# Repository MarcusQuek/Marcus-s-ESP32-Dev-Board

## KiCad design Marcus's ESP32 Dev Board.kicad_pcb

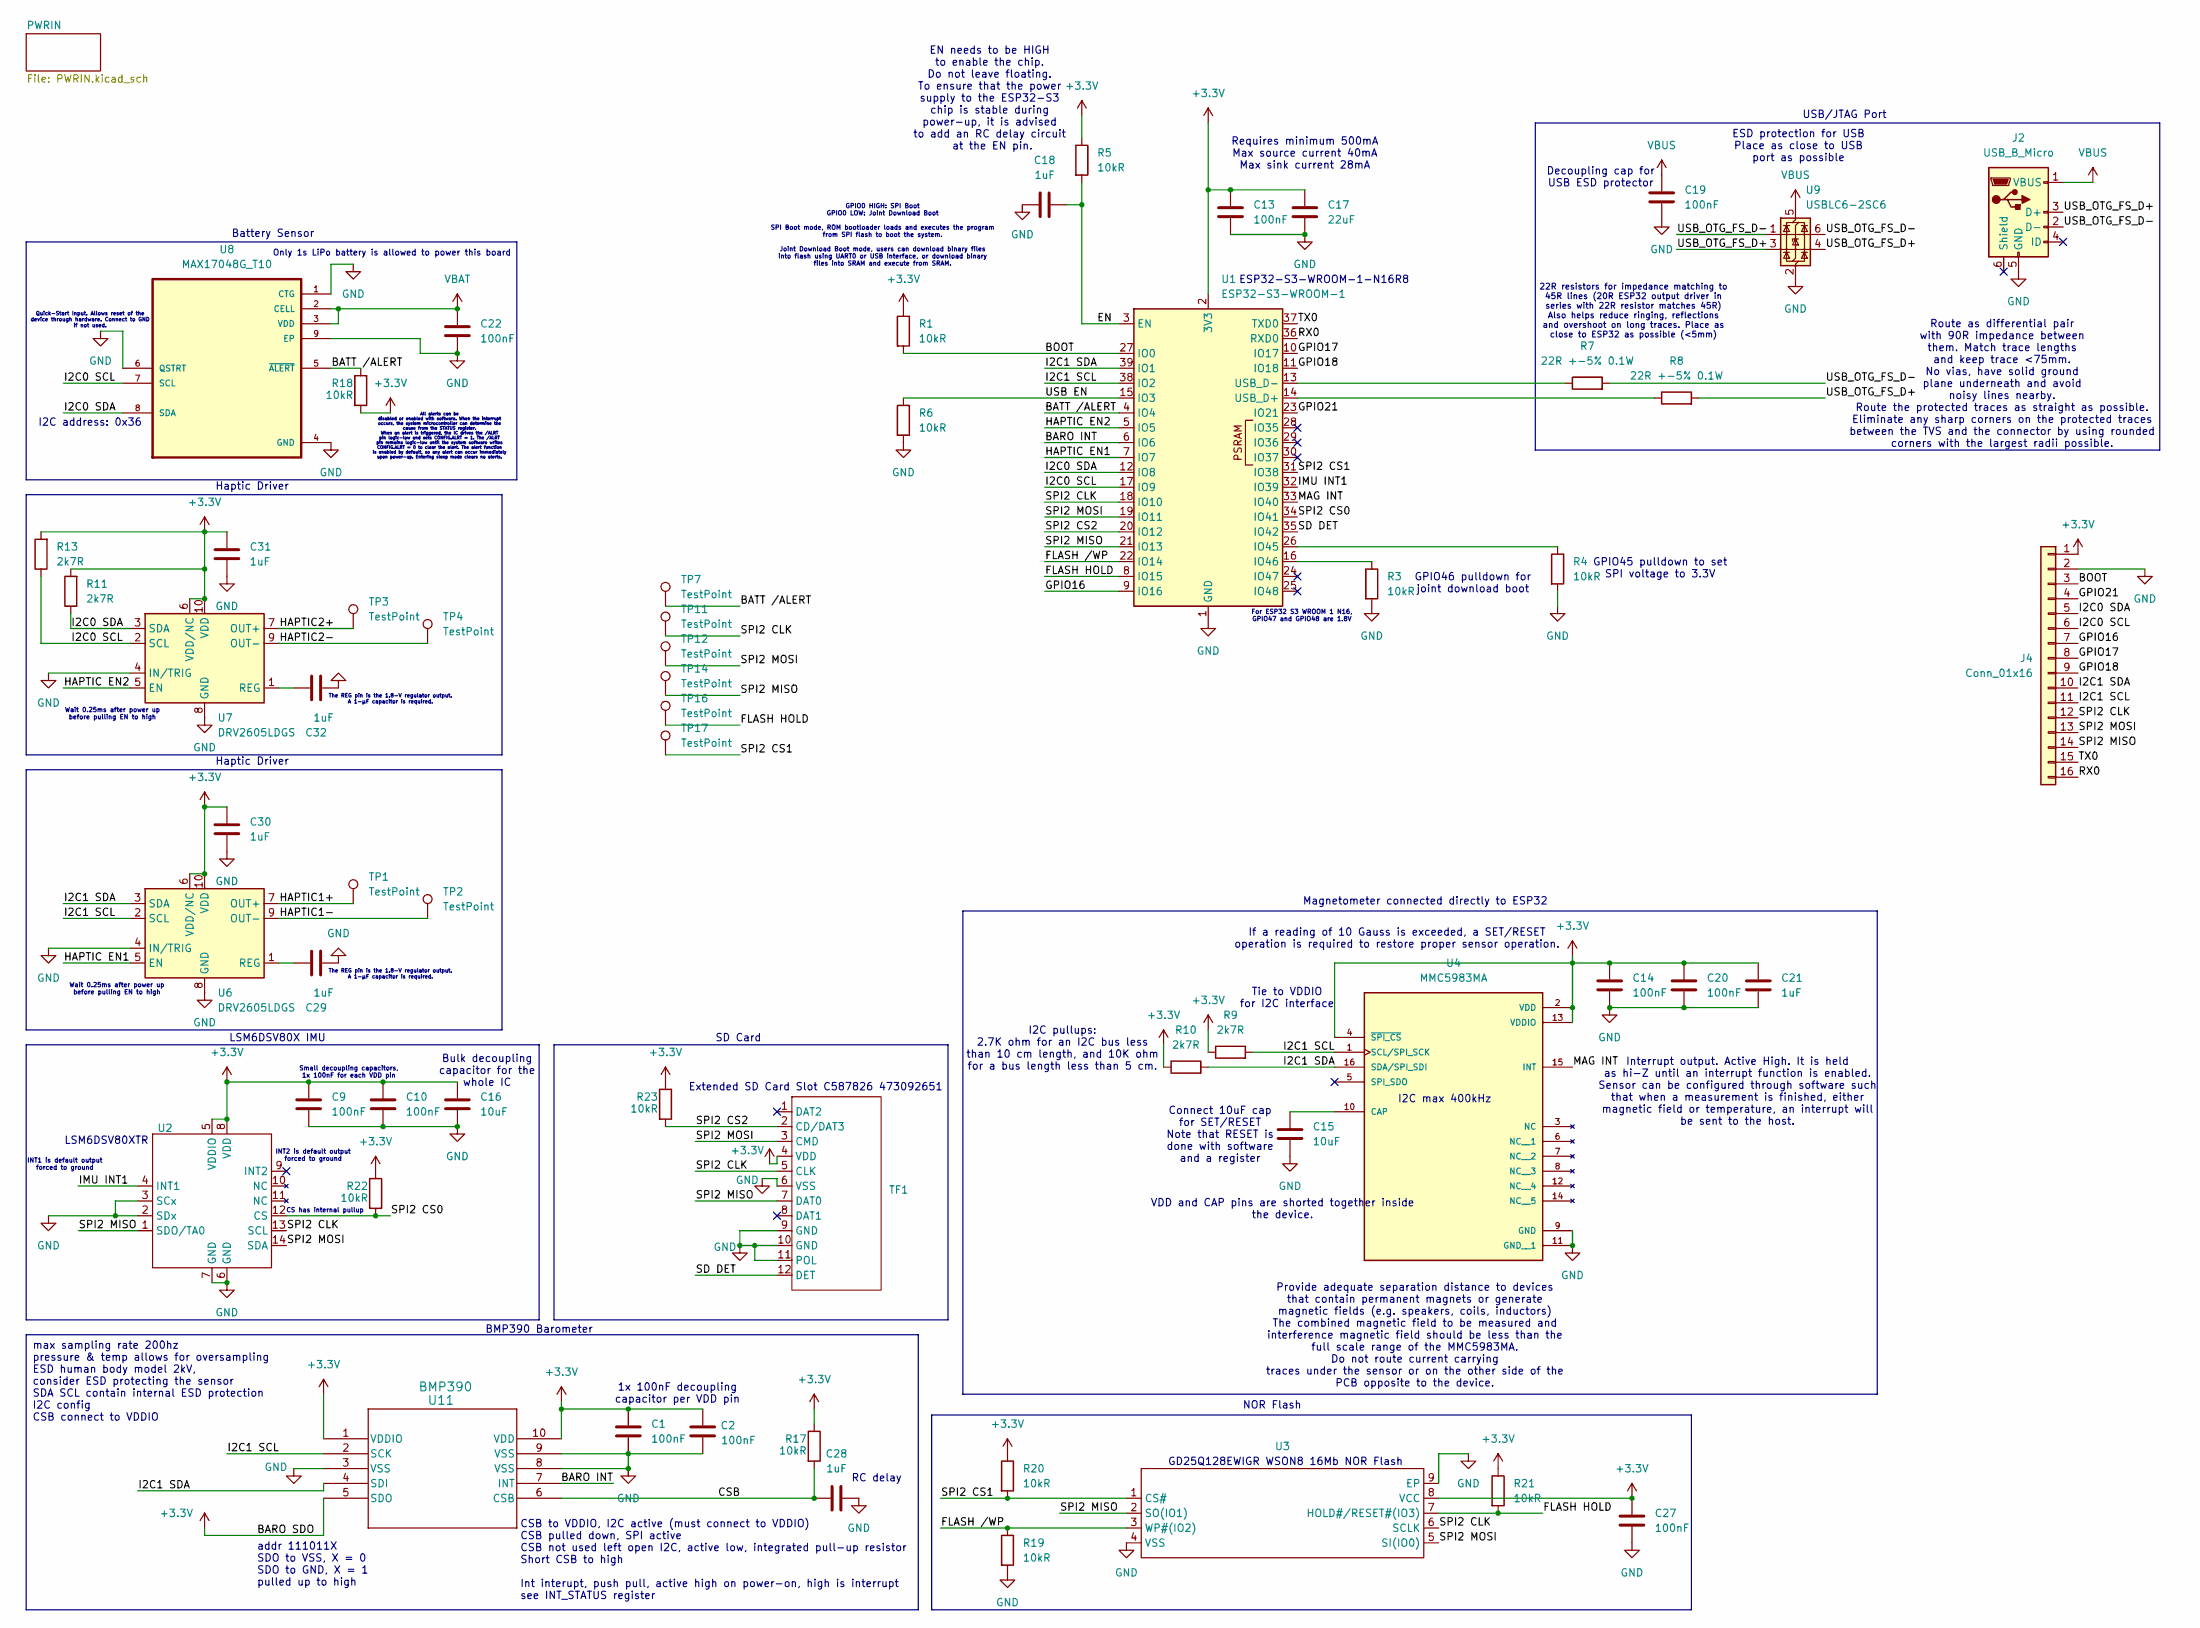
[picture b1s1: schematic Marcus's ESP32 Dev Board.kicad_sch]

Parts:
C1, C2, C9, C10, C13, C14, C19, C20, C22, C27: 100nF; C_0402_1005Metric
C15, C16: 10uF; C_0603_1608Metric
C17: 22uF; C_0805_2012Metric
C18, C21, C28, C29, C30, C31, C32: 1uF; C_0402_1005Metric
J2: USB_B_Micro; USB_Micro-B_GCT_USB3076-30-A
J4: Conn_01x16; PinHeader_1x16_P1.27mm_Vertical
R1, R3, R4, R5, R6, R17, R18, R19, R20, R21, R22, R23: 10kR; R_0201_0603Metric
R7, R8: 22R +-5% 0.1W; R_0201_0603Metric
R9, R10, R11, R13: 2k7R; C_0402_1005Metric
TF1: Extended SD Card Slot C587826 473092651; Manufacturer Part 473092651; LCSC Part Name 473092651
TP1, TP2, TP3, TP4: TestPoint; TestPoint_Pad_2.0x2.0mm
TP7, TP11, TP12, TP14, TP16, TP17: TestPoint; TestPoint_Pad_D1.0mm
U1: ESP32-S3-WROOM-1; ESP32-S3-WROOM-1U
U2: LGA-14_3x2.5mm_P0.5mm_LayoutBorder3x4y
U3: WSON-8-1EP_6x5mm_P1.27mm_EP3.4x4.3mm; Manufacturer Part GD25Q128EWIGR; LCSC Part Name 双路和四路串行闪存
U4: MMC5983MA; PARTREV A
U6, U7: DRV2605LDGS; VSSOP-10_3x3mm_P0.5mm
U8: MAX17048G_T10; MAX17048G+T10
U9: USBLC6-2SC6; SOT-23-6
U11: BMP390

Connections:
+3.3V: C1.1, C2.2, C9.1, C10.1, C13.1, C14.1, C16.1, C17.1, C20.1, C21.1, C27.1, C30.2, C31.2, J4.1, R1.1, R5.1, R9.1, R10.1, R11.2, R13.2, R17.1, R18.2, R20.1, R21.1, R22.1, R23.1, TF1.4 (VDD), U1.2 (3V3), U2.5 (VDDIO), U2.8 (VDD), U3.8 (VCC), U4.2 (VDD), U4.4 (~SPI_CS), U4.13 (VDDIO), U6.6 (VDD/NC), U6.10 (VDD), U7.6 (VDD/NC), U7.10 (VDD), U11.1 (VDDIO), U11.5 (SDO), U11.10 (VDD); also elsewhere on the board
/BARO INT: U1.6 (IO6), U11.7 (INT)
/BATT /ALERT: R18.1, TP7.1, U1.4 (IO4), U8.5 (~ALERT)
/BOOT: J4.3, R1.2, U1.27 (IO0)
/CSB: C28.1, R17.2, U11.6 (CSB)
/EN: C18.2, R5.2, U1.3 (EN)
/FLASH HOLD: R21.2, TP16.1, U1.8 (IO15), U3.7 (HOLD#/RESET#(IO3))
/FLASH /WP: R19.1, U1.22 (IO14), U3.3 (WP#(IO2))
/GPIO16: J4.7, U1.9 (IO16)
/GPIO17: J4.8, U1.10 (IO17)
/GPIO18: J4.9, U1.11 (IO18)
/GPIO21: J4.4, U1.23 (IO21)
/HAPTIC1+: TP1.1, U6.7 (OUT+)
/HAPTIC1-: TP2.1, U6.9 (OUT-)
/HAPTIC2+: TP3.1, U7.7 (OUT+)
/HAPTIC2-: TP4.1, U7.9 (OUT-)
/HAPTIC EN1: U1.7 (IO7), U6.5 (EN)
/HAPTIC EN2: U1.5 (IO5), U7.5 (EN)
/I2C0 SCL: J4.6, R13.1, U1.17 (IO9), U7.2 (SCL), U8.7 (SCL)
/I2C0 SDA: J4.5, R11.1, U1.12 (IO8), U7.3 (SDA), U8.8 (SDA)
/I2C1 SCL: J4.11, R9.2, U1.38 (IO2), U4.1 (SCL/SPI_SCK), U6.2 (SCL), U11.2 (SCK)
/I2C1 SDA: J4.10, R10.2, U1.39 (IO1), U4.16 (SDA/SPI_SDI), U6.3 (SDA), U11.4 (SDI)
/IMU INT1: U1.32 (IO39), U2.4 (INT1)
/MAG INT: U1.33 (IO40), U4.15 (INT)
/RX0: J4.16, U1.36 (RXD0)
/SD DET: TF1.12 (DET), U1.35 (IO42)
/SPI2 CLK: J4.12, TF1.5 (CLK), TP11.1, U1.18 (IO10), U2.13 (SCL), U3.6 (SCLK)
/SPI2 CS0: R22.2, U1.34 (IO41), U2.12 (CS)
/SPI2 CS1: R20.2, TP17.1, U1.31 (IO38), U3.1 (CS#)
/SPI2 CS2: R23.2, TF1.2 (CD/DAT3), U1.20 (IO12)
/SPI2 MISO: J4.14, TF1.7 (DAT0), TP14.1, U1.21 (IO13), U2.1 (SDO/TA0), U3.2 (SO(IO1))
/SPI2 MOSI: J4.13, TF1.3 (CMD), TP12.1, U1.19 (IO11), U2.14 (SDA), U3.5 (SI(IO0))
/TX0: J4.15, U1.37 (TXD0)
/USB EN: R6.1, U1.15 (IO3)
/USB_OTG_FS_D+: J2.3 (D+), R8.2, U9.3 (I/O2), U9.4 (I/O2)
/USB_OTG_FS_D-: J2.2 (D-), R7.2, U9.1 (I/O1), U9.6 (I/O1)
GND: C1.2, C2.1, C9.2, C10.2, C13.2, C14.2, C15.2, C16.2, C17.2, C18.1, C19.2, C20.2, C21.2, C22.2, C27.2, C28.2, C29.1, C30.1, C31.1, C32.1, J2.5 (GND), J4.2, R3.2, R4.2, R6.2, R19.2, TF1.6 (VSS), TF1.9 (GND), TF1.10 (GND), TF1.11 (POL), U1.1 (GND), U1.40 (GND), U1.41 (GND), U2.2 (SDx), U2.3 (SCx), U2.6 (GND), U2.7 (GND), U3.4 (VSS), U3.9 (EP), U4.9 (GND), U4.11 (GND__1), U6.4 (IN/TRIG), U6.8 (GND), U7.4 (IN/TRIG), U7.8 (GND), U8.1 (CTG), U8.4 (GND), U8.6 (QSTRT), U8.9 (EP), U9.2 (GND), U11.3 (VSS), U11.8 (VSS), U11.9 (VSS); also elsewhere on the board
unnamed: R4.1, U1.26 (IO45)
unnamed: R3.1, U1.16 (IO46)
unnamed: R8.1, U1.14 (USB_D+)
unnamed: R7.1, U1.13 (USB_D-)
unnamed: C15.1, U4.10 (CAP)
unnamed: C29.2, U6.1 (REG)
unnamed: C32.2, U7.1 (REG)
VBAT: C22.1, U8.2 (CELL), U8.3 (VDD); also elsewhere on the board
VBUS: C19.1, J2.1 (VBUS), U9.5 (VBUS); also elsewhere on the board

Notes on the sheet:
LSM6DSV80XTR
INT2 is default output forced to ground
I2C address: 0x36
Connect 10uF cap for SET/RESET Note that RESET is done with software and a register
EN needs to be HIGH to enable the chip. Do not leave floating. To ensure that the power supply to the ESP32-S3 chip is stable during power-up, it is advised to add an RC delay circuit at the EN pin.
ESP32-S3-WROOM-1-N16R8
ESD protection for USB Place as close to USB port as possible
CS has internal pullup
GPIO46 pulldown for joint download boot
VDD and CAP pins are shorted together inside the device.
Battery Sensor
GPIO45 pulldown to set SPI voltage to 3.3V
Route as differential pair with 90R impedance between them. Match trace lengths and keep trace <75mm. No vias, have solid ground plane underneath and avoid noisy lines nearby. Route the protected traces as straight as possible. Eliminate any sharp corners on the protected traces between the TVS and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
Wait 0.25ms after power up before pulling EN to high
Small decoupling capacitors, 1x 100nF for each VDD pin
I2C max 400kHz
LSM6DSV80X IMU
RC delay
Extended SD Card Slot C587826 473092651
Bulk decoupling capacitor for the whole IC
Haptic Driver
addr 111011X SDO to VSS, X = 0 SDO to GND, X = 1 pulled up to high
max sampling rate 200hz pressure & temp allows for oversampling ESD human body model 2kV, consider ESD protecting the sensor SDA SCL contain internal ESD protection I2C config CSB connect to VDDIO
Only 1s LiPo battery is allowed to power this board
For ESP32 S3 WROOM 1 N16, GPIO47 and GPIO48 are 1.8V
Magnetometer connected directly to ESP32
I2C pullups: 2.7K ohm for an I2C bus less than 10 cm length, and 10K ohm for a bus length less than 5 cm.
Tie to VDDIO for I2C interface
The REG pin is the 1.8-V regulator output. A 1-µF capacitor is required.
Interrupt output. Active High. It is held as hi-Z until an interrupt function is enabled. Sensor can be configured through software such that when a measurement is finished, either magnetic field or temperature, an interrupt will be sent to the host.
Requires minimum 500mA Max source current 40mA Max sink current 28mA
INT1 is default output forced to ground
BMP390 Barometer
1x 100nF decoupling capacitor per VDD pin
Quick-Start Input. Allows reset of the device through hardware. Connect to GND if not used.
NOR Flash
USB/JTAG Port
All alerts can be disabled or enabled with software. When the interrupt occurs, the system microcontroller can determine the cause from the STATUS register. When an alert is triggered, the IC drives the /ALRT pin logic-low and sets CONFIG.ALRT = 1. The /ALRT pin remains logic-low until the system s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
CSB to VDDIO, I2C active (must connect to VDDIO) CSB pulled down, SPI active CSB not used left open I2C, active low, integrated pull-up resistor Short CSB to high Int interupt, push pull, active high on power-on, high is interrupt see INT_STATUS register
22R resistors for impedance matching to 45R lines (20R ESP32 output driver in series with 22R resistor matches 45R) Also helps reduce ringing, reflections and overshoot on long traces. Place as close to ESP32 as possible (<5mm)

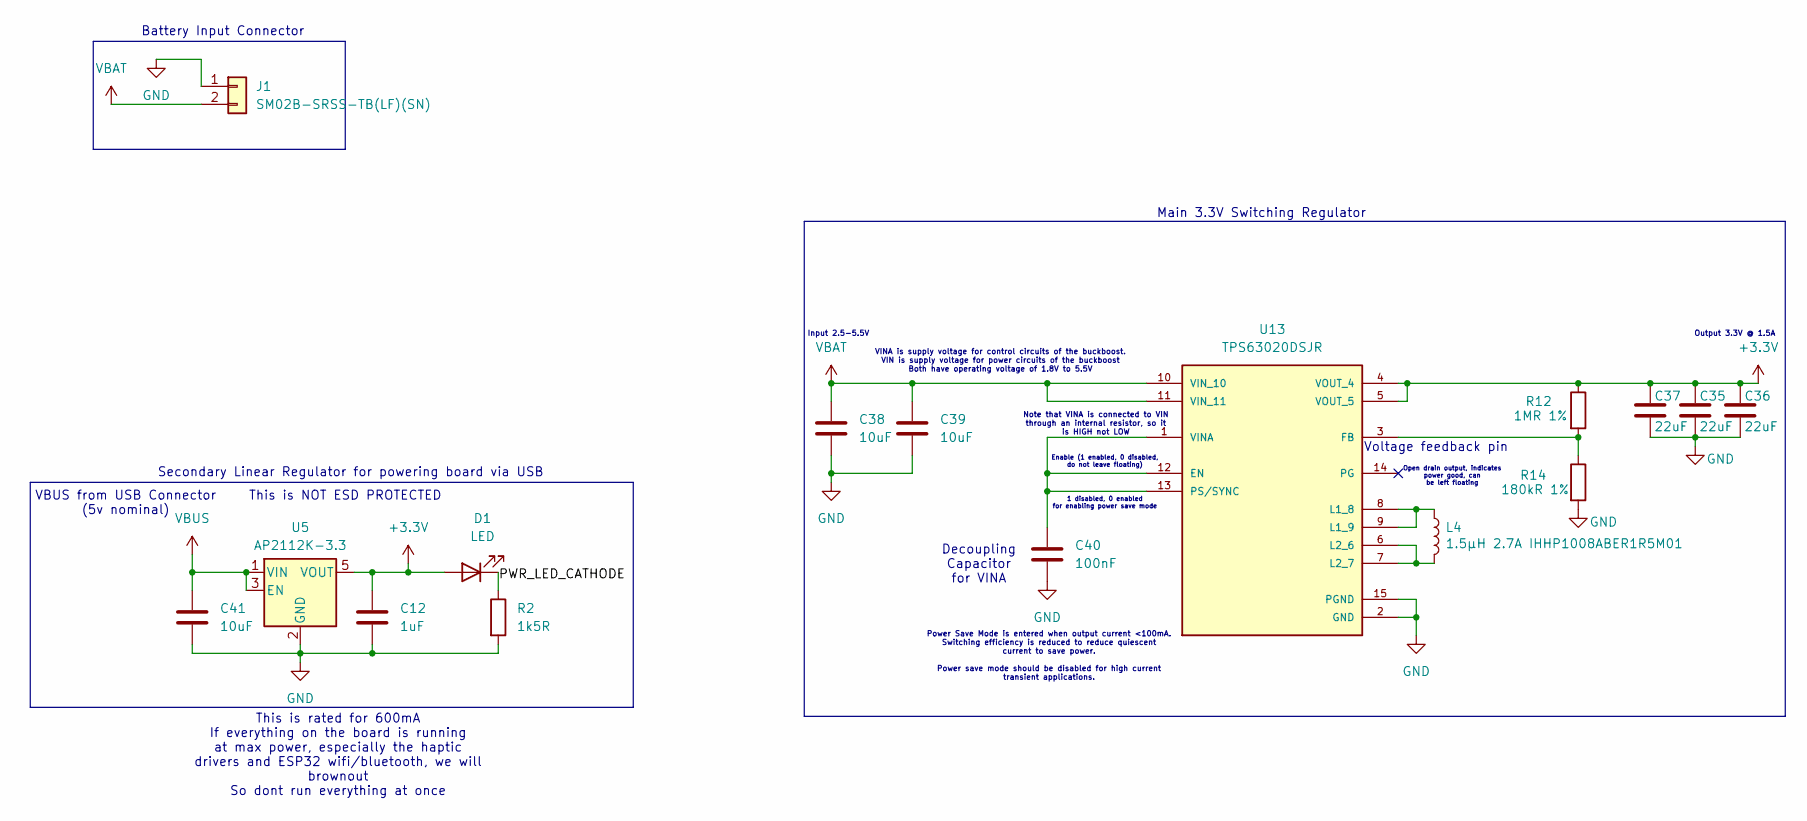
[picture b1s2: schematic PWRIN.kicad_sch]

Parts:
C12: 1uF; C_0402_1005Metric
C35, C36, C37: 22uF; C_0805_2012Metric
C38, C39, C41: 10uF; C_0603_1608Metric
C40: 100nF; C_0402_1005Metric
D1: LED; LED_0603_1608Metric
J1: SM02B-SRSS-TB(LF)(SN); JST_SH_SM02B-SRSS-TB_1x02-1MP_P1.00mm_Horizontal
L4: 1.5µH 2.7A IHHP1008ABER1R5M01; L_1008_2520Metric
R2: 1k5R; C_0402_1005Metric
R12: 1MR 1%; R_0201_0603Metric
R14: 180kR 1%; R_0201_0603Metric
U5: AP2112K-3.3; SOT-23-5
U13: TPS63020DSJR

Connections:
+3.3V: C12.1, C35.1, C36.1, C37.1, D1.2 (A), R12.1, U5.5 (VOUT), U13.4 (VOUT_4), U13.5 (VOUT_5); also elsewhere on the board
/PWRIN/PWR_LED_CATHODE: D1.1 (K), R2.1
GND: C12.2, C35.2, C36.2, C37.2, C38.2, C39.2, C40.2, C41.2, J1.1, R2.2, R14.2, U5.2 (GND), U13.2 (GND), U13.15 (PGND), U13.16, U13.18, U13.20, U13.22, U13.24, U13.26, U13.28, U13.30; also elsewhere on the board
unnamed: C40.1, U13.1 (VINA), U13.12 (EN), U13.13 (PS/SYNC)
unnamed: R12.2, R14.1, U13.3 (FB)
unnamed: L4.1, U13.8 (L1_8), U13.9 (L1_9)
unnamed: L4.2, U13.6 (L2_6), U13.7 (L2_7)
VBAT: C38.1, C39.1, J1.2, U13.10 (VIN_10), U13.11 (VIN_11); also elsewhere on the board
VBUS: C41.1, U5.1 (VIN), U5.3 (EN); also elsewhere on the board

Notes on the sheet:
Power Save Mode is entered when output current <100mA. Switching efficiency is reduced to reduce quiescent current to save power. Power save mode should be disabled for high current transient applications.
Note that VINA is connected to VIN through an internal resistor, so it is HIGH not LOW
This is NOT ESD PROTECTED
Voltage feedback pin
Secondary Linear Regulator for powering board via USB
Battery Input Connector
VINA is supply voltage for control circuits of the buckboost. VIN is supply voltage for power circuits of the buckboost Both have operating voltage of 1.8V to 5.5V
Decoupling Capacitor for VINA
1 disabled, 0 enabled for enabling power save mode
Enable (1 enabled, 0 disabled, do not leave floating)
Output 3.3V @ 1.5A
VBUS from USB Connector (5v nominal)
Open drain output, indicates power good, can be left floating
Input 2.5-5.5V
Main 3.3V Switching Regulator
This is rated for 600mA If everything on the board is running at max power, especially the haptic drivers and ESP32 wifi/bluetooth, we will brownout So dont run everything at once

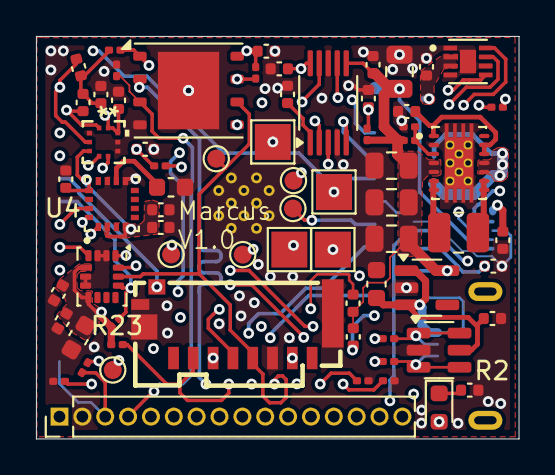
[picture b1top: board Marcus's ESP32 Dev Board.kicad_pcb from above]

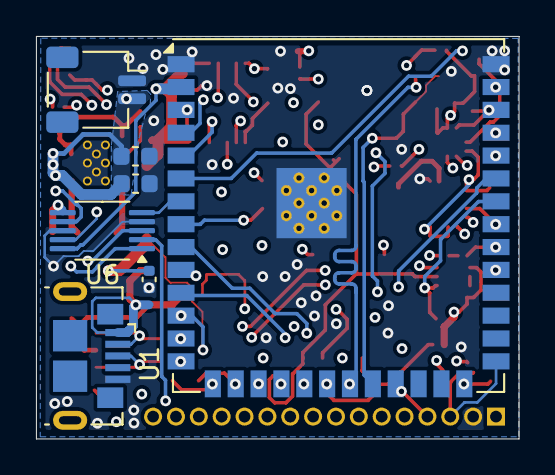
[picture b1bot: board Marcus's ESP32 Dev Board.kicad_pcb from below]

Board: 6 copper layers, 26.8 x 22.4 mm, 76 parts (7 on the bottom side), 51 nets.

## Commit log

2025-12-22 feat(pcb) split haptic drivers into different i2c buses
2025-12-22 feat(pcb) length match battery sensor i2c
2025-12-22 feat(pcb) add pullups to I2C0, move battery sensor to I2C0
2025-12-24 feat(pcb) cleanup and improve reliability
    add pullups to SPI CS lines, rearrange board slightly, add V1.0 silkscreen, increase size of VBUS input cap
2025-12-24 feat(cad) add 3d models
